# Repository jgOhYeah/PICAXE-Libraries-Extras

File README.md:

# PICAXE Libraries and Extras
Extra code and libraries I have written for PICAXE microcontrollers or making life easier when dealing with them.

Feedback / Improvements are welcome.

## LoRa and PJON drivers for SX127* based LoRa modules
Some code and modules for interfacing a PICAXE microcontroller to an SX127* based radio module. This code allows sending and receiving of raw LoRa packets and or encoding and decoding them using a limited implementation of the PJON protocol.

Click [here](LoRa%20and%20PJON/README.md) for more info.

## EEPROMTools
A python script and PICAXE code to read and write to EEPROM chips and save and restore from binary files. These files can be edited using your favourite hex editor and downloaded from or uploaded to the EEPROM chip connected to a PICAXE microcontroller using the EEPROMTools.py script.

### Example usage
###### Reading
```
./EEPROMTools.py r test.bin # Reads bytes 0 to 2047 (defaults) into test.bin
```
###### Writing
```
./EEPROMTools.py w 255 test.bin # Writes the first 255 bytes of test.bin into the first 255 bytes of the eeprom chip.
```

## Python Preprocessor
Implementation of a very simple and limited preprocessor for the PICAXE compiler.

Click [here](PythonPreprocessor/README.md) for more info.
[This preprocessor](https://github.com/Patronics/PicaxePreprocess) is very similar and has more features implemented, so I recommend that you use that one if you can.

## Musescore Tune Converter
A small Musescore 3 plugin to convert simple tunes into code that can be used by the PICAXE tune command.

Click [here](MusescoreTuneConverter/README.md) for more info.

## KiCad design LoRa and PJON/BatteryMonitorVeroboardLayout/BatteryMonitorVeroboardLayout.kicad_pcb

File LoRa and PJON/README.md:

# LoRa and PJON
Adapted from the Arduino [LoRa](https://github.com/sandeepmistry/arduino-LoRa) and [PJON](https://github.com/gioblu/PJON) libraries.
These code modules allow the PICAXE microcontroller to bit bang Serial Peripheral Interface (SPI) to Semtech SX127* based LoRa radio modules.

PICAXE microcontrollers are well suited for small sensors that these radio modules might be used in. This is because they are relatively cheap, can be run from 3.3V, are quite low current with the ability for reducing power draw further and have ability to be quickly and relatively easily reprogrammed in the field, as well as not needing many peripheries to be able to run.

Either LoRa packets as sent from the Arduino LoRa library can be transmitted and recieved or they can be encoded and decoded from a limited implementation of the PJON protocol, to add addressing and extra error detection.

Most of this code has been tested to run on a 14m2 or 18m2 with an Ra-01 module built around an SX1278 chip.

# Table of contents
- [LoRa and PJON](#lora-and-pjon)
- [Table of contents](#table-of-contents)
- [General code layout](#general-code-layout)
- [Configuration and Getting Started](#configuration-and-getting-started)
  - [Files to copy](#files-to-copy)
  - [Generating generated.basinc](#generating-generatedbasinc)
  - [Including the required files in your code](#including-the-required-files-in-your-code)
  - [Initialising the radio module](#initialising-the-radio-module)
  - [Setting the transmit power](#setting-the-transmit-power)
  - [Sending a LoRa packet](#sending-a-lora-packet)
  - [Receiving a LoRa packet](#receiving-a-lora-packet)
  - [Sending a PJON packet](#sending-a-pjon-packet)
  - [Receiving a PJON packet](#receiving-a-pjon-packet)
  - [Getting received RSSI and SNR values](#getting-received-rssi-and-snr-values)
  - [Power modes](#power-modes)
- [Hardware and Connections](#hardware-and-connections)
- [Limitations](#limitations)
  - [Overall](#overall)
  - [LoRa](#lora)
  - [PJON](#pjon)
- [Examples](#examples)
  - [Transmit.bas](#transmitbas)
  - [Receive.bas](#receivebas)
  - [PJONReceive.bas](#pjonreceivebas)
  - [BatteryVoltsMonitor.bas](#batteryvoltsmonitorbas)
- [Other code and info for using LoRa modules with PICAXE uCs](#other-code-and-info-for-using-lora-modules-with-picaxe-ucs)

# General code layout
The code for talking to the module is in [LoRa.basinc](include/LoRa.basinc). The code for dealing with PJON is in [PJON.basinc](include/PJON.basinc). Symbols and constants that might be needed globally are in [symbols.basinc](include/symbols.basinc) and [generated.basinc](include/generated.basinc).

Parameters are passed to most subroutines using the bytes `param1` and `param2`, although sometimes `rtrn` is used if a word is required.

Values are generally returned from sub routines using `rtrn`.

Many subroutines have what variables are modified by them or the subroutines they call in a comment up the top. This might be useful if weird things are happing as most convenient to use named variables (`b0, b1, ...`) are used during certain subroutines. No variables are required to store data between calling subroutines at the main program level, so they can be modified and used. Just expect them to change if a LoRa or PJON subroutine is called.

# Configuration and Getting Started
## Files to copy
Copy all of the [include](include) folder into your project folder.

## Generating [generated.basinc](include/generated.basinc)
Due to issues with program size and 32 bit maths, the spreading factor, frequency and ldo flag bytes need to be calculated before the program is uploaded to the microcontroller. This can be done with the python script [calculations.py](include/calculations.py) found in the include folder. Simply run this script from the include folder and follow the prompts to enter the frequency and spreading factor. If generated.basinc is placed somewhere else, copy and paste it into the include folder.

## Including the required files in your code
To include these modules, add these lines to the top of the main file.
```basic
#INCLUDE "include/symbols.basinc"
#INCLUDE "include/generated.basinc"

' Uncomment / comment out these according to what functionality is required.
#DEFINE ENABLE_LORA_RECEIVE
#DEFINE ENABLE_PJON_RECEIVE
' #DEFINE ENABLE_LORA_TRANSMIT
' #DEFINE ENABLE_PJON_TRANSMIT
```
To send / receive using PJON, the corresponding send / receive LoRa define must be present.

At the bottom of the file, include these lines:
```basic
' Libraries that will not be run first thing.
#INCLUDE "include/LoRa.basinc"
#INCLUDE "include/PJON.basinc"
```
[PJON.basinc](include/PJON.basinc) does not need to be included if it is not required. Make sure to use `end`, `stop` or an endless loop such as `goto main` to makes sure that the PICAXE does not run off the bottom of the main file into these files.

## Initialising the radio module
This code was designed and tested with the PICAXE running at 32MHz.
```basic
setfreq m32
```

The following will attempt to initialise the module. `rtrn` will be `0` on failure and `1` for success.
```basic
' Attempt to start the module
gosub begin_lora
if rtrn = 0 then
    sertxd("Failed to start LoRa", cr, lf)
    goto failed ' Endless loop and flashing an LED
else
    sertxd("LoRa Started", cr, lf)
endif
```

Next, the spread factor needs to be set to what was [defined](#generating-generatedbasinc) in [generated.basinc](include/generated.basinc).
```basic
gosub set_spreading_factor
```

## Setting the transmit power
By default, the transmit power is initialised to +17dBm, the same as with the Arduino LoRa library. This can be changed after initialisation by setting `param1` to be the new power in dBm and calling `set_tx_power`.
```basic
param1 = 17
gosub set_tx_power
```

Make sure to double check local regulations in regard to output power, frequencies allowed and transmission times.

## Sending a LoRa packet
Start by copying the packet contents into general ram and set `bptr` to point to the first byte.
```basic
eeprom 0, ("Hello world")

bptr = 28
for counter2 = 0 to 10
	read counter2, @bptrinc
next counter2

bptr = 28 ' Point back to the fist byte
```
Begin a packet and set up the registers in the module ready to transmit.
```basic
gosub begin_lora_packet
```
Set `param1` to the length of the packet. This must be after calling `begin_lora_packet`.
```basic
param1 = 11
```

Next, call `write_lora` to send the data stored in the PICAXE's ram to the buffer in the module.
```basic
gosub write_lora
```

Finally, call `end_lora_packet` to tell the module to send the packet and wait until it is done. If the packet sent successfully, `rtrn` will be `1`. Sometimes the connection to the module may not be the most reliable and a timeout is implemented to stop the PICAXE getting stuck forever. In this case, `rtrn` will be `0`.
```basic
gosub end_lora_packet
if rtrn = 0 then
    ' Something went wrong. Attempt to reinitialise the radio module.
    sertxd("LoRa dropped out.", cr, lf)
endif
```

## Receiving a LoRa packet
Before any packet can be received, the module must be put into listening mode. This increases the current draw quite dramatically - see the [Power Modes](#power-modes) section for more details.
```basic
gosub setup_lora_receive
```

Check the status of the `DIO0` pin using the `LORA_RECEIVED` macro. If this is true, then a packet has been received and it should be processed. Call `setup_lora_read` to start this process.
```basic
if LORA_RECEIVED then
    gosub setup_lora_read
    ...
```

A packet is valid if, after calling `setup_lora_read`, `rtrn` is not `LORA_RECEIVED_CRC_ERROR`. If it is valid, `rtrn` will contain the received packet length.
```basic
    ...
    if rtrn != LORA_RECEIVED_CRC_ERROR then
        ' Do stuff with the received packet
    endif
endif
```

The packet contents can be obtained by calling `read_lora`. Each time `read_lora` is called, the next byte will be returned in `rtrn`.
```basic
for total_length = total_length to 1 step -1
    gosub read_lora
    sertxd(rtrn)
next total_length
```

## Sending a PJON packet
The process for sending a PJON packet is similar to sending a standared LoRa packet, except with calls to different subroutines.

Start by calling `begin_pjon_packet` to set `bptr` to the correct starting location.
```basic
gosub begin_pjon_packet
```

Now, `@bptrinc` can be used to load the data into the correct location in ram.
```basic
' This is an example. Use a for loop or something better in actual practise
@bptrinc = "H"
@bptrinc = "e"
@bptrinc = "l"
@bptrinc = "l"
@bptrinc = "o"
@bptrinc = " "
@bptrinc = "W"
@bptrinc = "o"
@bptrinc = "r"
@bptrinc = "l"
@bptrinc = "d"
```

Set `param1` to be the address that the packet should be sent to. Address 0 is a broadcast to everything else on the network.
```basic
param1 = 255
```

The packet can be finalised, checksums calculated, headers added and the packet sent by calling `end_pjon_packet`. If the packet is sent successfully, `rtrn = 1`, else `rtrn = 0`. 
```basic
gosub end_pjon_packet
if rtrn = 0 then
    ' Something went wrong. Attempt to reinitialise the radio module.
    sertxd("LoRa dropped out.", cr, lf)
endif
```

## Receiving a PJON packet
Before any packet can be received, the module must be put into listening mode. This increases the current draw quite dramatically - see the [Power Modes](#power-modes) section for more details.
```basic
gosub setup_lora_receive
```

Check the status of the `DIO0` pin using the `LORA_RECEIVED` macro. If this is true, then a packet has been received and it should be processed. Call `read_pjon_packet` to start this process. If the packet is valid, addressed to us and meets the checksum, the `rtrn` will contain the length of the packet payload. Otherwise, `rtrn = PJON_INVALID_PACKET`.
```basic
gosub read_pjon_packet
if rtrn != PJON_INVALID_PACKET then
    ...
```

The sender id is contained in `param1`. If the sender id was not included, `param1 = 0`.

To access the payload, use `@bptrinc`. `bptr` points to the first byte in the payload after calling `read_pjon_packet` and it returned a success.
```basic
for rtrn = rtrn to 1 step -1
	sertxd(#@bptrinc,", ")
next total_length
```

## Getting received RSSI and SNR values
The RSSI of a received packet can be obtained by calling `packet_rssi`. The RSSI is returned as a 2's compliment integer in dBm.
```basic
gosub packet_rssi
' rtrn = rssi in 2's complement
gosub print_signed ' Extra freebe to show how to interpret it.

print_signed:
	' Prints the value stored in rtrn as a 2s complement signed integer
	tmpwd = rtrn & 0x8000
	if tmpwd != 0 then
		; Negative
		sertxd("-")
		tmpwd = rtrn ^ 0xffff + 1 ' Convert to positive
		sertxd(#tmpwd)
	else
		sertxd(#rtrn)
	endif
	return
```

The signal to noise ratio of a received packet can be obtained using `packet_snr`. After calling this, `rtrn` will be the signal to noise ratio in 2's complement multiplied by 4 (to allow > whole number accuracy).
```basic
gosub packet_snr

' Note: I can't remember if there is a bug in this printing bit.
tmpwd = rtrn % 4 * 5 / 2 ; First digit after decimal point
rtrn = rtrn / 4
sertxd(cr,lf,"  - SNR: ")
gosub print_signed
sertxd(".",#tmpwd,cr,lf)
```

## Power modes
The LoRa modules have several different power modes and features available in each of them. Using a multimeter measuring current to the entire circuit, including an MIC2954 linear regulator dropping from 18V, I measured:
| LoRa Module Mode    | Picaxe Mode                      | Current draw     |
| ------------------- | -------------------------------- | ---------------- |
| Idle                | 32MHz                            | 4.95mA           |
| Sleep               | 32MHz                            | 3.16mA           |
| Sleep               | nap, brownout detection disabled | 0.18mA to 0.25mA |
| Receiving           | 32MHz                            | 14mA             |
| During transmission | 32MHz                            | ~150mA           |

My understanding is that idle allows use of the First In, First Out (FIFO) buffer in the module, while sleep clears it and doesn't let it be accessed or written to. This could be wrong though.

Subroutines that require it will automatically put the module in idle mode, but if needed somewhere else, use:
```basic
gosub idle_lora
```

To enter sleep mode:
```basic
gosub sleep_lora
```

To enter receiving mode:
```basic
gosub setup_lora_receive
```

# Hardware and Connections
The connections are defined in [symbols.basic](include/symbols.basinc). Pretty much any GPIO pins can be used. `MISO` and `DIO0` are inputs, everything else are outputs.

The schematic below shows the connections as originally given in [symbols.basic](include/symbols.basinc), including an LED and the programming header.

# Limitations
## Overall
- Both libraries use a fairly significant number of variables. Most subroutines should have which ones are modified by them or any subroutines that they call as a guide, but they may not be up to date or missing.
- This takes up a significant amount of the available program memory, so there is not that much left for the code that drives this code.

## LoRa
- As the SPI connection to the module is bit banged, it blocks any other code from running while talking to the module.
- When running at 32MHz, the clock speed is about 1.58kHz. For context, the radio module is rated to 10MHz and Arduino Unos drive it at 8MHz by default, meaning fairly slow setup and data transfer.
- Certain values must be calculated before the program is sent to the chip and cannot be changed at runtime. These include the frequency and spreading factor.
- Currently the `DIO0` pin on the radio module is used to detect when a packet is received, requiring an extra input pin on the PICAXE. This is due to the slow speed of the SPI bus and amount of time that would be spent checking registers otherwise, although feel free to implement that version as well.
- Explicit header mode only is supported. This means that spread factor 6 is also not supported due to its reliance on implicit header mode. Personally, I have found spread factor 9 to be one of the better settings in terms of received RSSI.
- Certain other configurations such as changing RF power pins are not supported.

## PJON
- Currently, only local mode is supported (no bus id).
- There is no queue of packets. It is assumed a packet will be processed as it is received and the `end_pjon_packet` subtroutine will block any other code running until the packet is sent.
- All packets are sent with a CRC32 checksum, regardless of length. It would probably be fairly easy to implement automatic selection of checksums based on packet length. When receiving, both CRC8 and CRC32 checksums are accepted.
- The sender id will always be sent.

# Examples
## [Transmit.bas](Transmit.bas)
This is a simple example demonstrating transmission of raw LoRa packets that initialises the module and repeatedly sends "Hello World" once every few seconds.

## [Receive.bas](Receive.bas)
This is a simple example demonstrating receiving of raw LoRa packets. This initialises the module and prints information about any packet it receives to the serial port.

## [PJONReceive.bas](PJONReceive.bas)
This example demonstrates the use of the PJON module to receive and print PJON formatted packets to the serial port.

## [BatteryVoltsMonitor.bas](BatteryVoltsMonitor.bas)
This is a project of mine using these modules. It can be found [here](https://github.com/jgOhYeah/Farm-PJON-LoRa-network)

# Other code and info for using LoRa modules with PICAXE uCs
- [HABAXE](https://picaxeforum.co.uk/threads/habaxe2-a-lora-based-high-altitude-balloon-tracker-project.26699/) is a High Altitude Baloon tracker built around x2 series chips and SX1278 based radio modules. It can also use them to transmit FSK modulated data as well as LoRa.
- This [PICAXE forum thread](https://picaxeforum.co.uk/threads/sx126x-lora-modules.31380/) discusses the use of SX12**6*** based LoRa modules, which can communicate over UART, making them much simpler to drive for a PICAXE, as well as having some better specs and features.

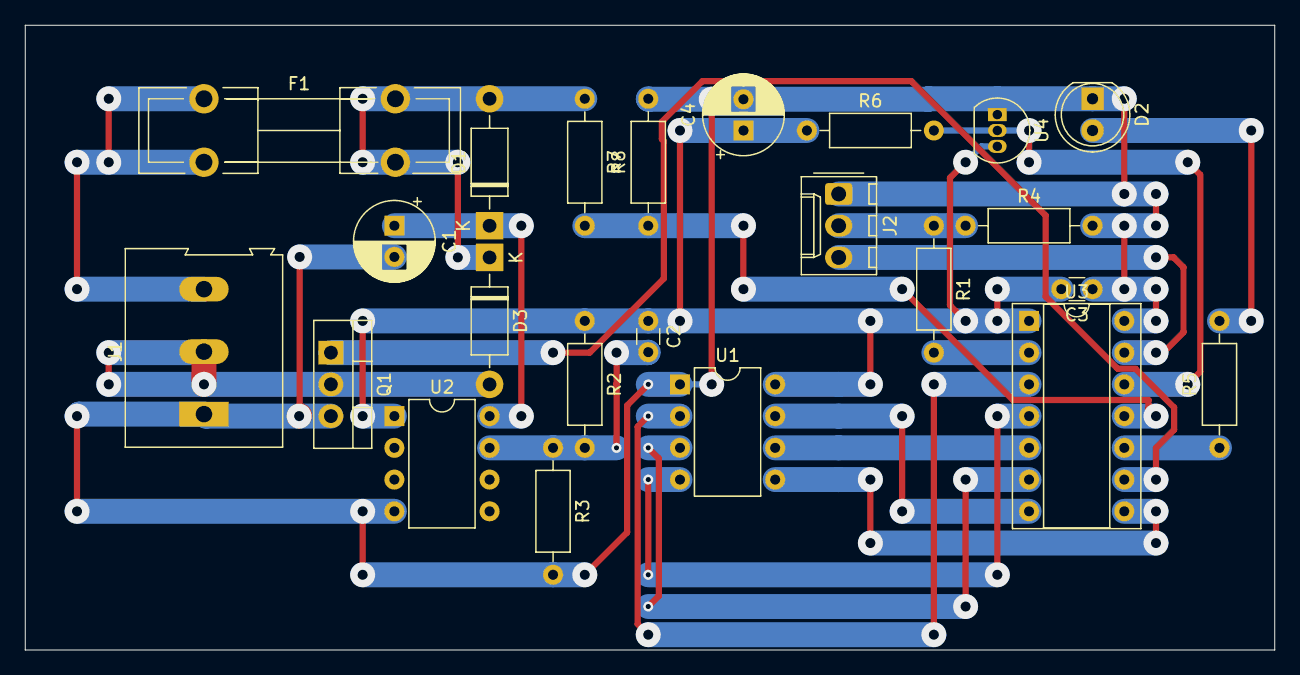
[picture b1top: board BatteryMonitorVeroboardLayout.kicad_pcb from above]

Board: 2 copper layers, 100.0 x 50.0 mm, 23 parts (0 on the bottom side), 21 nets.

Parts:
C1: 100uF; CP_Radial_D6.3mm_P2.50mm
C2: 100pF; C_Disc_D3.0mm_W1.6mm_P2.50mm
C3: 100n; C_Disc_D3.0mm_W1.6mm_P2.50mm
C4: 3.3uF; CP_Radial_D6.3mm_P2.50mm
D1, D3: 1N4004; D_DO-41_SOD81_P10.16mm_Horizontal
D2: LED; LED_D5.0mm
F1: 250mA; Fuseholder5x20_horiz_open_lateral_Type-II
J1: Screw_Terminal_01x03; TerminalBlock_Altech_AK300-3_P5.00mm
J2: Conn_01x03; Molex_KK-254_AE-6410-03A_1x03_P2.54mm_Vertical
Q1: IRLB8721PBF; TO-220-3_Vertical
R1: 22k; R_Axial_DIN0207_L6.3mm_D2.5mm_P10.16mm_Horizontal
R2: 330k; R_Axial_DIN0207_L6.3mm_D2.5mm_P10.16mm_Horizontal
R3: 220k; R_Axial_DIN0207_L6.3mm_D2.5mm_P10.16mm_Horizontal
R4: 10k; R_Axial_DIN0207_L6.3mm_D2.5mm_P10.16mm_Horizontal
R5: 470; R_Axial_DIN0207_L6.3mm_D2.5mm_P10.16mm_Horizontal
R6, R8: 4.7k; R_Axial_DIN0207_L6.3mm_D2.5mm_P10.16mm_Horizontal
R7: 33k; R_Axial_DIN0207_L6.3mm_D2.5mm_P10.16mm_Horizontal
U1: SX1278 LoRa Module; DIP-8_W7.62mm
U2: MIC2954; DIP-8_W7.62mm
U3: PICAXE-14M; DIP-14_W7.62mm_Socket
U4: DS18B20; TO-92_Inline

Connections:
+3V3: C2.1, C3.2, C4.1, R2.1, R6.1, U1.8, U2.1, U3.1, U4.3
+BATT: D1.2, D3.1, F1.2, R7.1
GNDREF: C1.2, C3.1, C4.2, D2.1, J1.1, J2.1, Q1.3, R3.2, R4.2, R8.2, U1.1, U2.4, U3.14, U4.1
unnamed: C1.1, D1.1, U2.8
unnamed: C2.2, R2.2, R3.1, U2.7
unnamed: D2.2, R5.2
unnamed: D3.2, J1.2, Q1.2
unnamed: F1.1, J1.3
unnamed: J2.2, R1.1, R4.1
unnamed: J2.3, U3.13
unnamed: Q1.1, U3.9
unnamed: R1.2, U3.2
unnamed: R5.1, U3.10
unnamed: R6.2, U3.12, U4.2
unnamed: R7.2, R8.1, U3.11
unnamed: U1.2, U3.3
unnamed: U1.3, U3.6
unnamed: U1.4, U3.4
unnamed: U1.5, U3.8
unnamed: U1.6, U3.5
unnamed: U1.7, U3.7

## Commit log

2020-12-02 Added preprocessor script
2020-12-02 Fixed small formatting issues
2020-12-12 Added link to a similar preprocessor
2020-12-13 Added picaxe tune converter
2020-12-19 Added stronger hint to use the other preprocessor
2021-01-27 Adding LoRa and PJON code
2021-01-27 Move Battery Monitor Example to its own repository
2021-02-09 Tweaked to compile LoRa w standard preprocessor
2021-04-03 Added EEPROMTools & some stack depth comments LoRa
2021-04-03 Add description of EEPROMTools
2021-04-03 Updated defaults
2023-02-20 Cleaning up, added interactive EEPROM tools from another repository.
2023-02-22 Added option to not include LoRa setup (synchronised with pump monitor code)
2024-01-26 Added varuable analyser
2024-01-26 Prints out variable usage and finds unused variables.
